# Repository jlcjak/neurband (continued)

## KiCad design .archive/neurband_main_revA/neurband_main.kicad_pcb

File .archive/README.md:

# Archive (`.archive/`)

The folder name starts with a dot so Backplane's project and part lists skip it; git and GitHub still show it.

Older work, kept for reference. Nothing here is current or ordered (every fab file here has
`"order": false`).

| Folder | What it is |
|---|---|
| `neurband_main_revA/` | Rev A main board: 16 channels, ESP32-S3, 54 × 34 mm ([docs/DESIGN.md](../docs/DESIGN.md)) |
| `neurband_main_revB/` | Rev B main board: compact 16 channels, unfinished |
| `neurband_electrodes_revB/` | Rev B electrode flex in four sizes |
| `mech_revAB/` | Rev A/B mechanics: housing, pod shells, strap, fit checks ([docs/mech/mechanical.md](../docs/mech/mechanical.md)). The scripts import `mech/cadutil.py` and `mech/fitgeom.py` |
| `neurband_c_layout_scripts/` | The one-off scripts used while laying out the rev C main board. They record how it was done; the board file itself is now the source. They expect to run from `boards/neurband_c/layout/` |
| `local/` | Local-only backups (working copies, layout build backups); not in git |

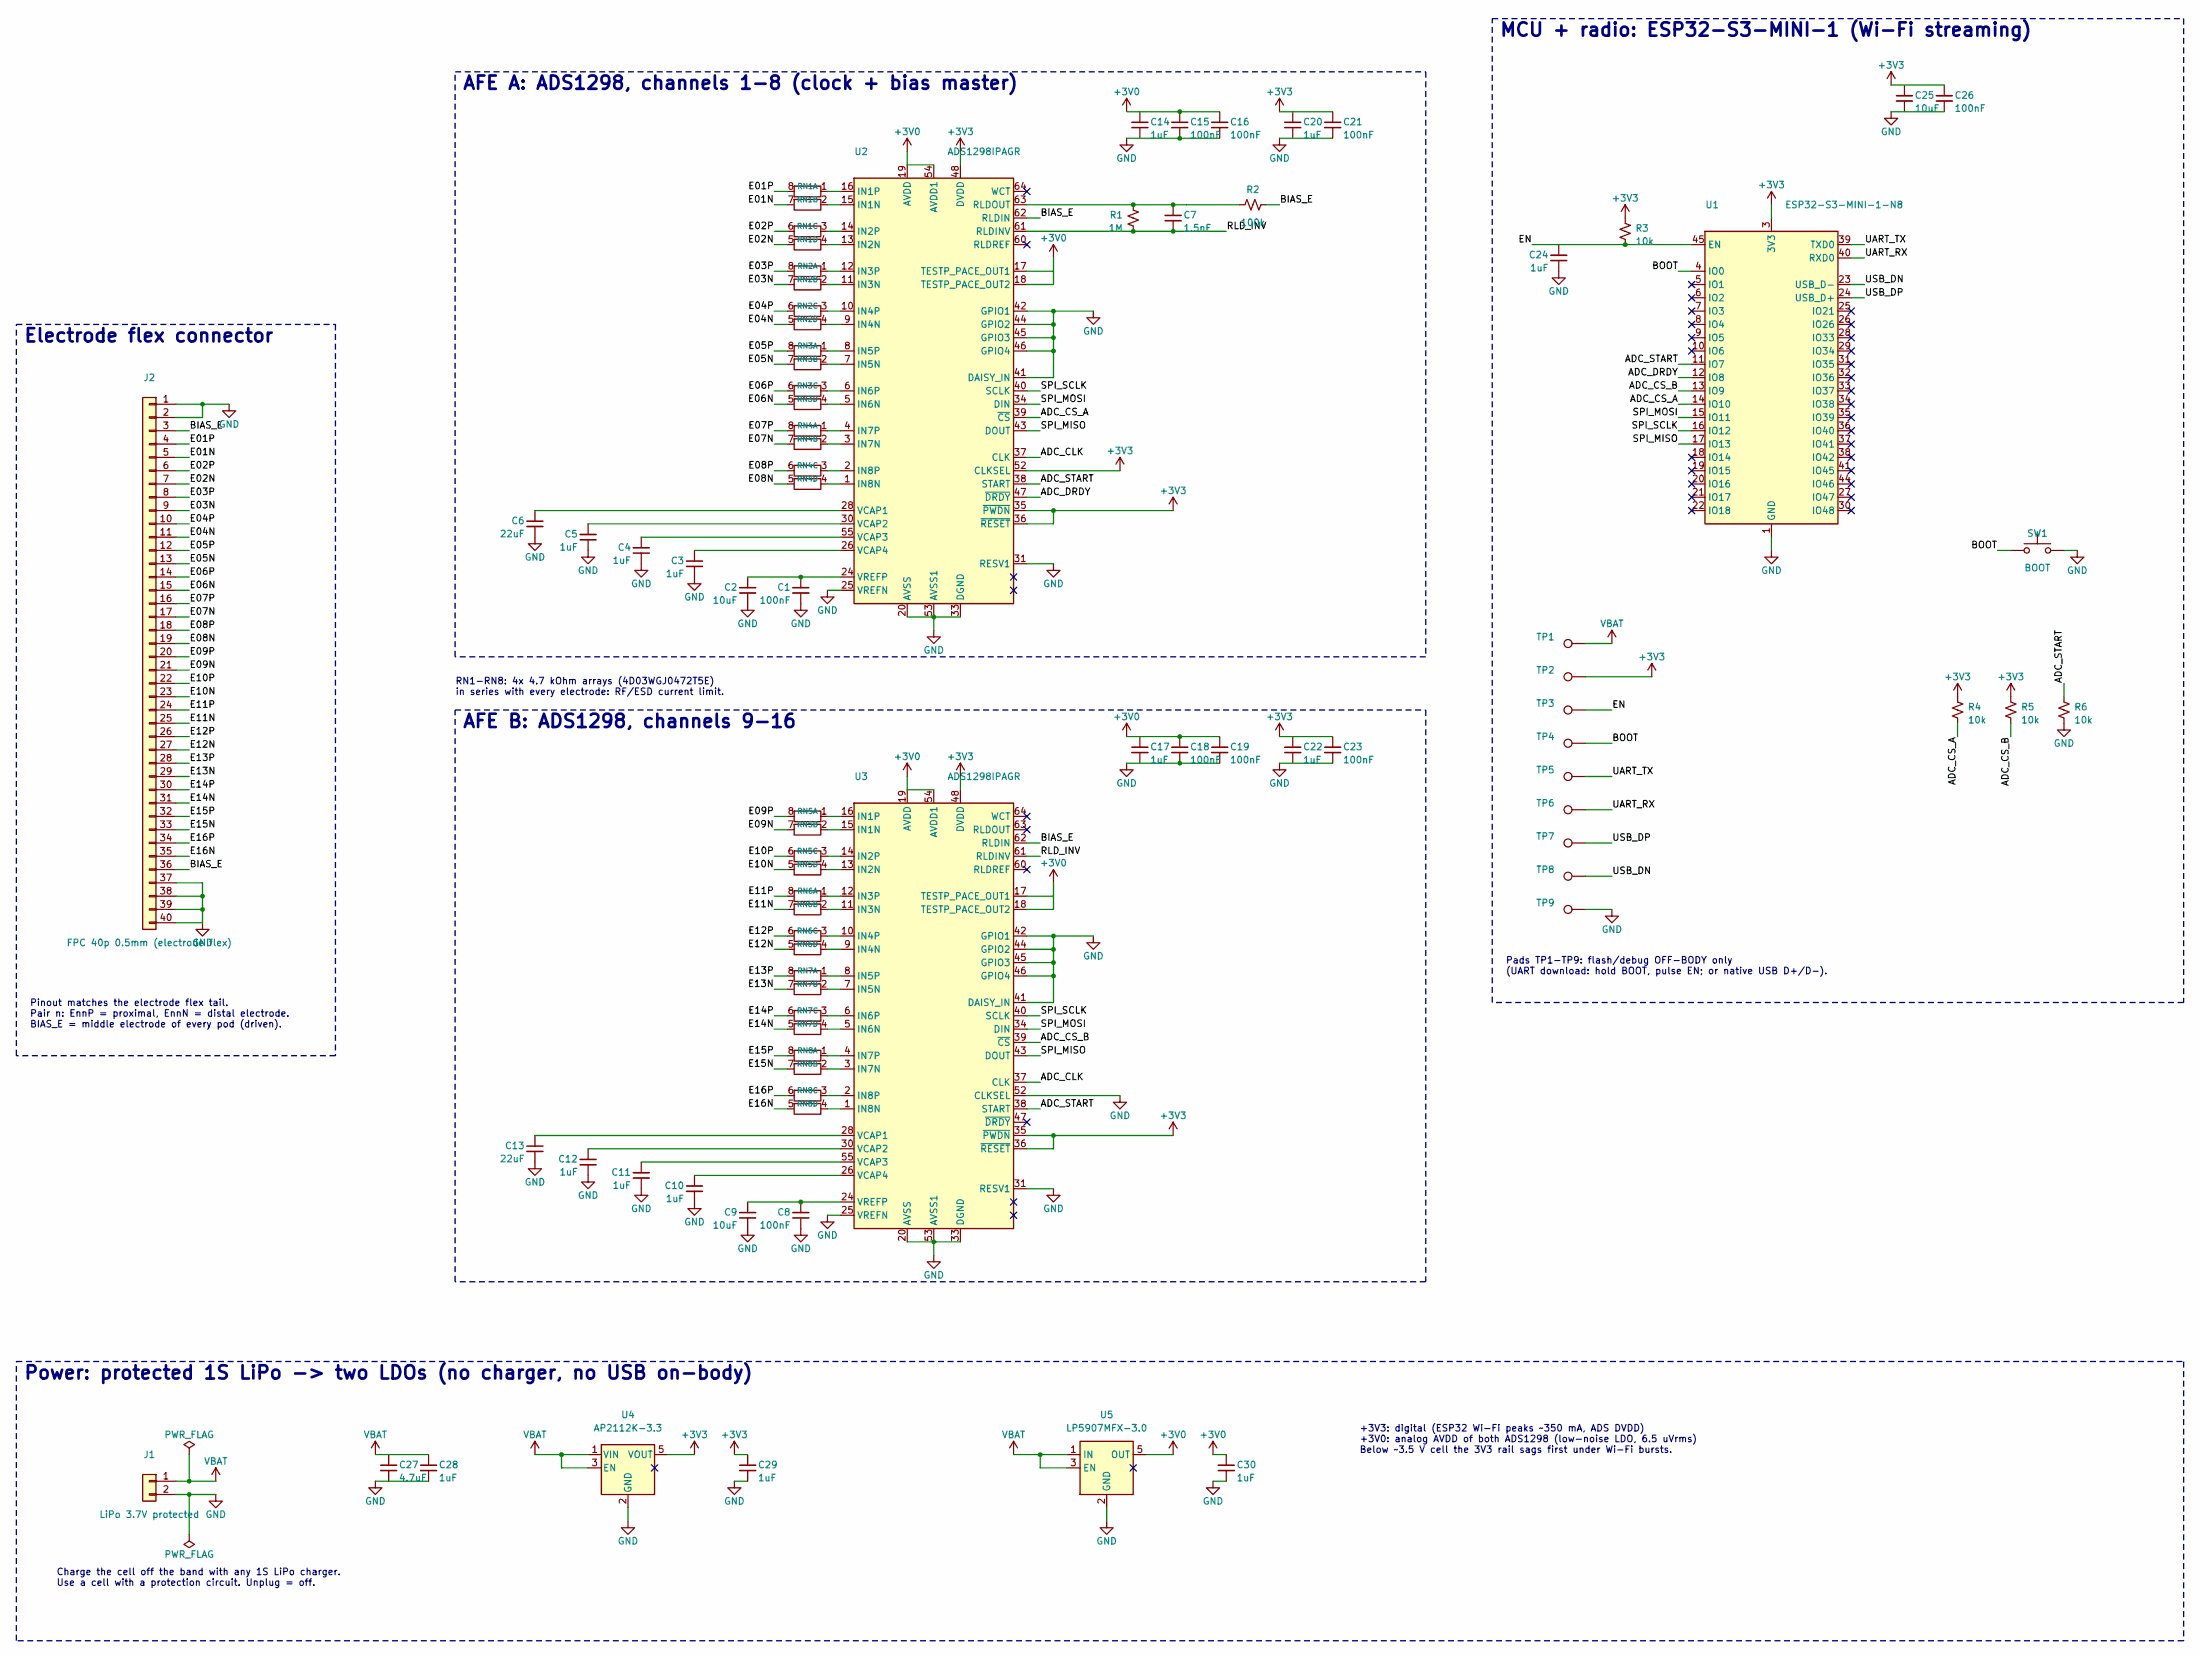
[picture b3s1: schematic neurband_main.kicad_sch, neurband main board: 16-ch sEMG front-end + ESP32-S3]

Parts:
C1, C8, C15, C16, C18, C19, C21, C23, C26: 100nF; C_0402_1005Metric; MPN CL05B104KO5NNNC; LCSC C1525
C2, C9, C25: 10uF; C_0603_1608Metric; MPN CL10A106KP8NNNC; LCSC C19702
C3, C4, C5, C10, C11, C12, C14, C17, C20, C22, C24, C28, C29, C30: 1uF; C_0402_1005Metric; MPN CL05A105KA5NQNC; LCSC C52923
C6, C13: 22uF; C_0603_1608Metric; MPN CL10A226MQ8NRNC; LCSC C59461
C7: 1.5nF; C_0402_1005Metric; MPN CC0402KRX7R9BB152; LCSC C107022
C27: 4.7uF; C_0603_1608Metric; MPN CL10A475KO8NNNC; LCSC C19666
J1: LiPo 3.7V protected; JST_SH_SM02B-SRSS-TB_1x02-1MP_P1.00mm_Horizontal; MPN SM02B-SRSS-TB(LF)(SN); LCSC C160402
J2: FPC 40p 0.5mm (electrode flex); HCTL_HC-FPC-05-09-40RLTAG_1x40-1MP_P0.50mm_Horizontal; MPN HC-FPC-05-09-40RLTAG; LCSC C5213762
R1: 1M; R_0402_1005Metric; MPN 0402WGF1004TCE; LCSC C26083
R2: 100k; R_0402_1005Metric; MPN 0402WGF1003TCE; LCSC C25741
R3, R4, R5, R6: 10k; R_0402_1005Metric; MPN 0402WGF1002TCE; LCSC C25744
RN1, RN2, RN3, RN4, RN5, RN6, RN7, RN8: 4.7k; R_Array_Convex_4x0603; MPN 4D03WGJ0472T5E; LCSC C1980
SW1: BOOT; SW_SPST_TS-1088-xR020; MPN TS-1088-AR02016; LCSC C720477
TP1, TP2, TP3, TP4, TP5, TP6, TP7, TP8, TP9: pad; TestPoint_Pad_1.0x1.0mm
U1: ESP32-S3-MINI-1-N8; MPN ESP32-S3-MINI-1-N8; LCSC C2913206
U2, U3: ADS1298IPAGR; TQFP-64_10x10mm_P0.5mm; MPN ADS1298IPAGR; LCSC C527440
U4: AP2112K-3.3; SOT-23-5; MPN AP2112K-3.3TRG1; LCSC C51118
U5: LP5907MFX-3.0; SOT-23-5; MPN LP5907MFX-3.0/NOPB; LCSC C475492

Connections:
+3V0: C14.1, C15.1, C16.1, C17.1, C18.1, C19.1, C30.1, U2.17 (TESTP_PACE_OUT1), U2.18 (TESTP_PACE_OUT2), U2.19 (AVDD), U2.21 (AVDD), U2.22 (AVDD), U2.54 (AVDD1), U2.56 (AVDD), U2.59 (AVDD), U3.17 (TESTP_PACE_OUT1), U3.18 (TESTP_PACE_OUT2), U3.19 (AVDD), U3.21 (AVDD), U3.22 (AVDD), U3.54 (AVDD1), U3.56 (AVDD), U3.59 (AVDD), U5.5 (OUT)
+3V3: C20.1, C21.1, C22.1, C23.1, C25.1, C26.1, C29.1, R3.1, R4.1, R5.1, TP2.1 (1_1), U1.3 (3V3), U2.35 (~PWDN), U2.36 (~RESET), U2.48 (DVDD), U2.50 (DVDD), U2.52 (CLKSEL), U3.35 (~PWDN), U3.36 (~RESET), U3.48 (DVDD), U3.50 (DVDD), U4.5 (VOUT)
/ADC_CLK: U2.37 (CLK), U3.37 (CLK)
/ADC_CS_A: R4.2, U1.14 (IO10), U2.39 (~CS)
/ADC_CS_B: R5.2, U1.13 (IO9), U3.39 (~CS)
/ADC_DRDY: U1.12 (IO8), U2.47 (~DRDY)
/ADC_START: R6.1, U1.11 (IO7), U2.38 (START), U3.38 (START)
/BIAS_E: J2.3, J2.36, R2.2, U2.62 (RLDIN), U3.62 (RLDIN)
/BOOT: SW1.1, TP4.1 (1_1), U1.4 (IO0)
/E01N: J2.5, RN1.7 (R2.2)
/E01P: J2.4, RN1.8 (R1.2)
/E02N: J2.7, RN1.5 (R4.2)
/E02P: J2.6, RN1.6 (R3.2)
/E03N: J2.9, RN2.7 (R2.2)
/E03P: J2.8, RN2.8 (R1.2)
/E04N: J2.11, RN2.5 (R4.2)
/E04P: J2.10, RN2.6 (R3.2)
/E05N: J2.13, RN3.7 (R2.2)
/E05P: J2.12, RN3.8 (R1.2)
/E06N: J2.15, RN3.5 (R4.2)
/E06P: J2.14, RN3.6 (R3.2)
/E07N: J2.17, RN4.7 (R2.2)
/E07P: J2.16, RN4.8 (R1.2)
/E08N: J2.19, RN4.5 (R4.2)
/E08P: J2.18, RN4.6 (R3.2)
/E09N: J2.21, RN5.7 (R2.2)
/E09P: J2.20, RN5.8 (R1.2)
/E10N: J2.23, RN5.5 (R4.2)
/E10P: J2.22, RN5.6 (R3.2)
/E11N: J2.25, RN6.7 (R2.2)
/E11P: J2.24, RN6.8 (R1.2)
/E12N: J2.27, RN6.5 (R4.2)
/E12P: J2.26, RN6.6 (R3.2)
/E13N: J2.29, RN7.7 (R2.2)
/E13P: J2.28, RN7.8 (R1.2)
/E14N: J2.31, RN7.5 (R4.2)
/E14P: J2.30, RN7.6 (R3.2)
/E15N: J2.33, RN8.7 (R2.2)
/E15P: J2.32, RN8.8 (R1.2)
/E16N: J2.35, RN8.5 (R4.2)
/E16P: J2.34, RN8.6 (R3.2)
/EN: C24.1, R3.2, TP3.1 (1_1), U1.45 (EN)
/RLD_INV: C7.2, R1.2, U2.61 (RLDINV), U3.61 (RLDINV)
/SPI_MISO: U1.17 (IO13), U2.43 (DOUT), U3.43 (DOUT)
/SPI_MOSI: U1.15 (IO11), U2.34 (DIN), U3.34 (DIN)
/SPI_SCLK: U1.16 (IO12), U2.40 (SCLK), U3.40 (SCLK)
/UART_RX: TP6.1 (1_1), U1.40 (RXD0)
/UART_TX: TP5.1 (1_1), U1.39 (TXD0)
/USB_DN: TP8.1 (1_1), U1.23 (USB_D-)
/USB_DP: TP7.1 (1_1), U1.24 (USB_D+)
GND: C1.2, C2.2, C3.2, C4.2, C5.2, C6.2, C8.2, C9.2, C10.2, C11.2, C12.2, C13.2, C14.2, C15.2, C16.2, C17.2, C18.2, C19.2, C20.2, C21.2, C22.2, C23.2, C24.2, C25.2, C26.2, C27.2, C28.2, C29.2, C30.2, J1.2, J2.1, J2.2, J2.37, J2.38, J2.39, J2.40, R6.2, SW1.2, TP9.1 (1_1), U1.1 (GND), U1.2 (GND), U1.42 (GND), U1.43 (GND), U1.46 (GND), U1.47 (GND), U1.48 (GND), U1.49 (GND), U1.50 (GND), U1.51 (GND), U1.52 (GND), U1.53 (GND), U1.54 (GND), U1.55 (GND), U1.56 (GND), U1.57 (GND), U1.58 (GND), U1.59 (GND), U1.60 (GND), U1.61 (GND), U1.62 (GND), U1.63 (GND), U1.64 (GND), U1.65 (GND), U2.20 (AVSS), U2.23 (AVSS), U2.25 (VREFN), U2.31 (RESV1), U2.32 (AVSS), U2.33 (DGND), U2.41 (DAISY_IN), U2.42 (GPIO1), U2.44 (GPIO2), U2.45 (GPIO3), U2.46 (GPIO4), U2.49 (DGND), U2.51 (DGND), U2.53 (AVSS1), U2.57 (AVSS), U2.58 (AVSS), U3.20 (AVSS), U3.23 (AVSS), U3.25 (VREFN), U3.31 (RESV1), U3.32 (AVSS), U3.33 (DGND), U3.41 (DAISY_IN), U3.42 (GPIO1), U3.44 (GPIO2), U3.45 (GPIO3), U3.46 (GPIO4), U3.49 (DGND), U3.51 (DGND), U3.52 (CLKSEL), U3.53 (AVSS1), U3.57 (AVSS), U3.58 (AVSS), U4.2 (GND), U5.2 (GND)
unnamed: RN1.1 (R1.1), U2.16 (IN1P)
unnamed: RN1.2 (R2.1), U2.15 (IN1N)
unnamed: RN1.3 (R3.1), U2.14 (IN2P)
unnamed: RN1.4 (R4.1), U2.13 (IN2N)
unnamed: RN2.1 (R1.1), U2.12 (IN3P)
unnamed: RN2.2 (R2.1), U2.11 (IN3N)
unnamed: RN2.3 (R3.1), U2.10 (IN4P)
unnamed: RN2.4 (R4.1), U2.9 (IN4N)
unnamed: RN3.1 (R1.1), U2.8 (IN5P)
unnamed: RN3.2 (R2.1), U2.7 (IN5N)
unnamed: RN3.3 (R3.1), U2.6 (IN6P)
unnamed: RN3.4 (R4.1), U2.5 (IN6N)
unnamed: RN4.1 (R1.1), U2.4 (IN7P)
unnamed: RN4.2 (R2.1), U2.3 (IN7N)
unnamed: RN4.3 (R3.1), U2.2 (IN8P)
unnamed: RN4.4 (R4.1), U2.1 (IN8N)
unnamed: RN5.1 (R1.1), U3.16 (IN1P)
unnamed: RN5.2 (R2.1), U3.15 (IN1N)
unnamed: RN5.3 (R3.1), U3.14 (IN2P)
unnamed: RN5.4 (R4.1), U3.13 (IN2N)
unnamed: RN6.1 (R1.1), U3.12 (IN3P)
unnamed: RN6.2 (R2.1), U3.11 (IN3N)
unnamed: RN6.3 (R3.1), U3.10 (IN4P)
unnamed: RN6.4 (R4.1), U3.9 (IN4N)
unnamed: RN7.1 (R1.1), U3.8 (IN5P)
unnamed: RN7.2 (R2.1), U3.7 (IN5N)
unnamed: RN7.3 (R3.1), U3.6 (IN6P)
unnamed: RN7.4 (R4.1), U3.5 (IN6N)
unnamed: RN8.1 (R1.1), U3.4 (IN7P)
unnamed: RN8.2 (R2.1), U3.3 (IN7N)
unnamed: RN8.3 (R3.1), U3.2 (IN8P)
unnamed: RN8.4 (R4.1), U3.1 (IN8N)
unnamed: C7.1, R1.1, R2.1, U2.63 (RLDOUT)
unnamed: C6.1, U2.28 (VCAP1)
unnamed: C5.1, U2.30 (VCAP2)
unnamed: C4.1, U2.55 (VCAP3)
unnamed: C3.1, U2.26 (VCAP4)
unnamed: C1.1, C2.1, U2.24 (VREFP)
unnamed: C13.1, U3.28 (VCAP1)
unnamed: C12.1, U3.30 (VCAP2)
unnamed: C11.1, U3.55 (VCAP3)
unnamed: C10.1, U3.26 (VCAP4)
unnamed: C8.1, C9.1, U3.24 (VREFP)
VBAT: C27.1, C28.1, J1.1, TP1.1 (1_1), U4.1 (VIN), U4.3 (EN), U5.1 (IN), U5.3 (EN)

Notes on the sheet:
Electrode flex connector
Pinout matches the electrode flex tail. Pair n: EnnP = proximal, EnnN = distal electrode. BIAS_E = middle electrode of every pod (driven).
RN1-RN8: 4x 4.7 kOhm arrays (4D03WGJ0472T5E) in series with every electrode: RF/ESD current limit.
AFE A: ADS1298, channels 1-8 (clock + bias master)
AFE B: ADS1298, channels 9-16
Pads TP1-TP9: flash/debug OFF-BODY only (UART download: hold BOOT, pulse EN; or native USB D+/D-).
MCU + radio: ESP32-S3-MINI-1 (Wi-Fi streaming)
Charge the cell off the band with any 1S LiPo charger. Use a cell with a protection circuit. Unplug = off.
+3V3: digital (ESP32 Wi-Fi peaks ~350 mA, ADS DVDD) +3V0: analog AVDD of both ADS1298 (low-noise LDO, 6.5 uVrms) Below ~3.5 V cell the 3V3 rail sags first under Wi-Fi bursts.
Power: protected 1S LiPo -> two LDOs (no charger, no USB on-body)

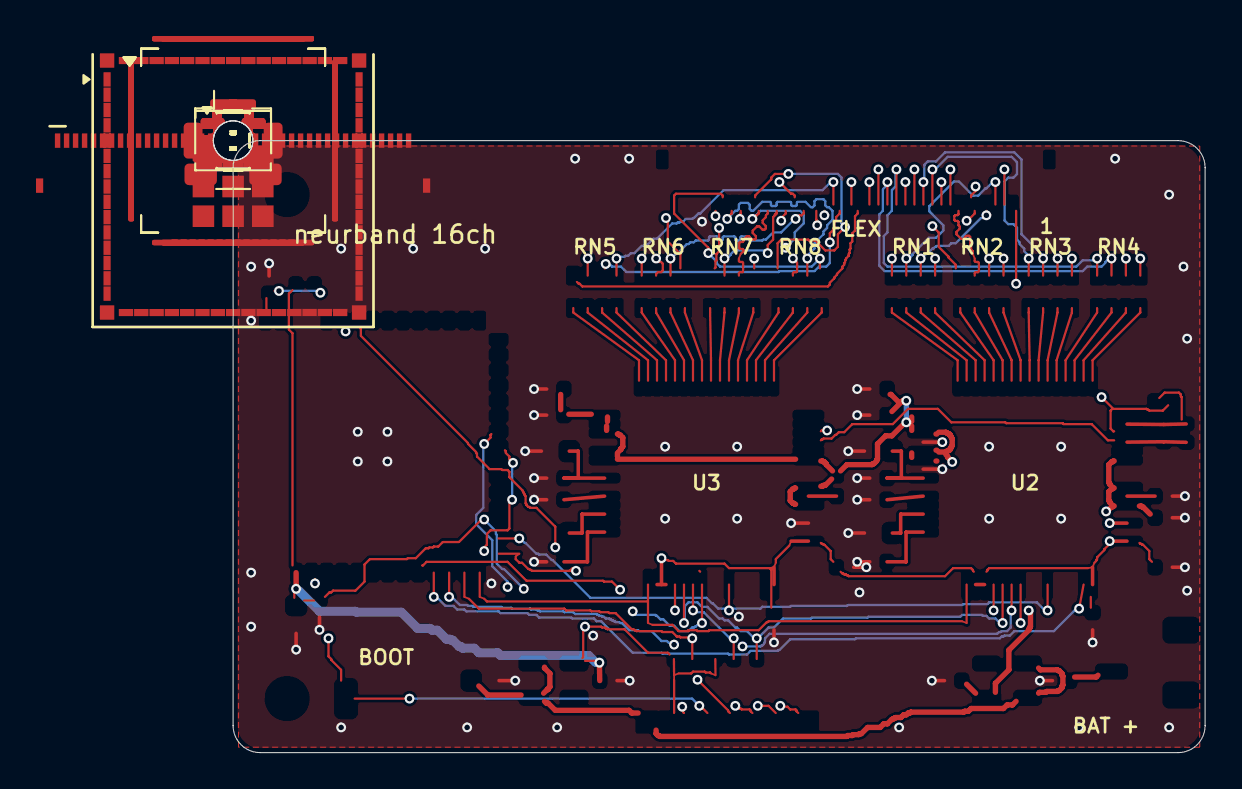
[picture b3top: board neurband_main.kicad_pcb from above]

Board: 4 copper layers, 54.0 x 34.0 mm, 63 parts (0 on the bottom side), 95 nets.

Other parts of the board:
H1, H2: M2; MountingHole_2.2mm_M2

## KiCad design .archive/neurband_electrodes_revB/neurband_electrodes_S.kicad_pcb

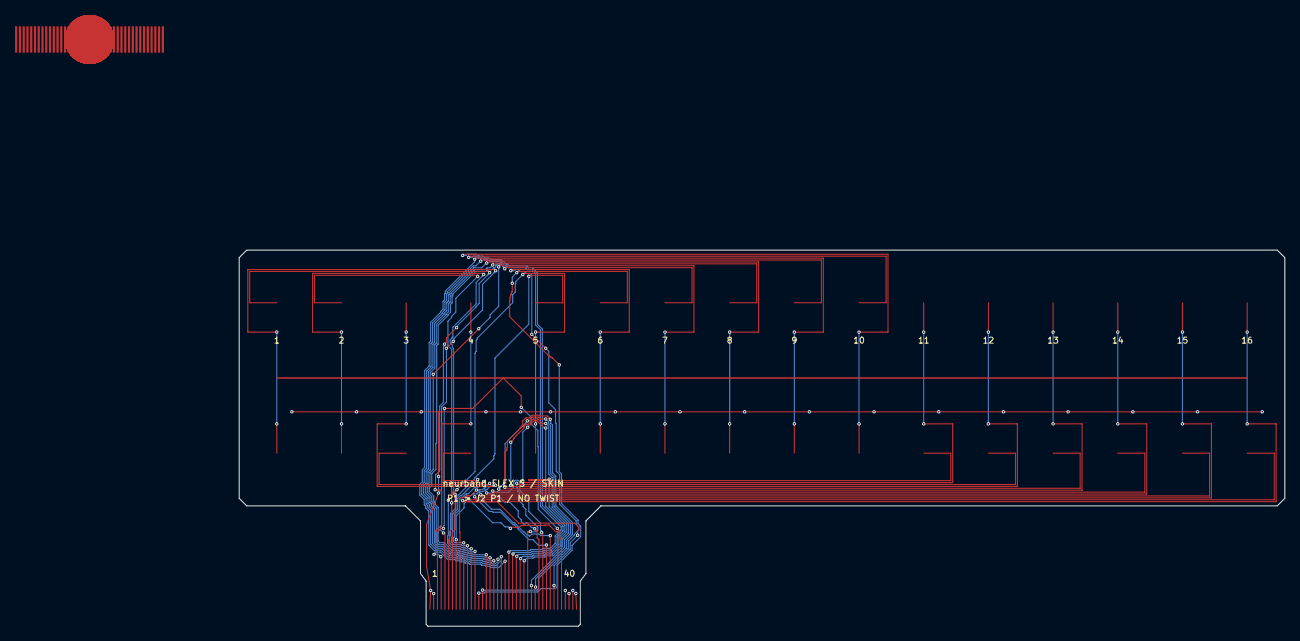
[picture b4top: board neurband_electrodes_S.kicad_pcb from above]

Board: 2 copper layers, 139.0 x 50.0 mm, 49 parts (0 on the bottom side), 34 nets.

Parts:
E1B, E2B, E3B, E4B, E5B, E6B, E7B, E8B, E9B, E10B, E11B, E12B, E13B, E14B, E15B, E16B: electrode B; Electrode_D6.5mm
E1N, E2N, E3N, E4N, E5N, E6N, E7N, E8N, E9N, E10N, E11N, E12N, E13N, E14N, E15N, E16N: electrode N; Electrode_D6.5mm
E1P, E2P, E3P, E4P, E5P, E6P, E7P, E8P, E9P, E10P, E11P, E12P, E13P, E14P, E15P, E16P: electrode P; Electrode_D6.5mm
J1: Tail 40 fingers 0.5mm; FPC_Tail_40_P0.5mm

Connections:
/BIAS_E: E1B.1, E2B.1, E3B.1, E4B.1, E5B.1, E6B.1, E7B.1, E8B.1, E9B.1, E10B.1, E11B.1, E12B.1, E13B.1, E14B.1, E15B.1, E16B.1, J1.3, J1.36
/E01N: E1N.1, J1.5
/E01P: E1P.1, J1.4
/E02N: E2N.1, J1.7
/E02P: E2P.1, J1.6
/E03N: E3N.1, J1.9
/E03P: E3P.1, J1.8
/E04N: E4N.1, J1.11
/E04P: E4P.1, J1.10
/E05N: E5N.1, J1.13
/E05P: E5P.1, J1.12
/E06N: E6N.1, J1.15
/E06P: E6P.1, J1.14
/E07N: E7N.1, J1.17
/E07P: E7P.1, J1.16
/E08N: E8N.1, J1.19
/E08P: E8P.1, J1.18
/E09N: E9N.1, J1.21
/E09P: E9P.1, J1.20
/E10N: E10N.1, J1.23
/E10P: E10P.1, J1.22
/E11N: E11N.1, J1.25
/E11P: E11P.1, J1.24
/E12N: E12N.1, J1.27
/E12P: E12P.1, J1.26
/E13N: E13N.1, J1.29
/E13P: E13P.1, J1.28
/E14N: E14N.1, J1.31
/E14P: E14P.1, J1.30
/E15N: E15N.1, J1.33
/E15P: E15P.1, J1.32
/E16N: E16N.1, J1.35
/E16P: E16P.1, J1.34
GND: J1.1, J1.2, J1.37, J1.38, J1.39, J1.40

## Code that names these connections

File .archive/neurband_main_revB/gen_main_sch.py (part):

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    s.wire([pts[0], pts[-1]])
    for p in pts[1:-1]:
        s.junction(*p)
    if grp[0] == 1:  # pin 3 (BIAS_E) is just below: take GND off the top of the rail
        s.junction(*pts[0])
        s.wire([pts[0], (pts[0][0] + 5.08, pts[0][1])])
        s.power("GND", pts[0][0] + 5.08, pts[0][1])
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    s.power("GND", x, gy1 + 2.54)
    # right side
    s.pin_nc(u, "WCT")
    s.pin_nc(u, "RLDREF")
    s.pin_nc(u, "27")
    s.pin_nc(u, "29")
    # TESTP/TESTN unused -> AVDD (datasheet note 1)
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    s.wire([(t1x + 5.08, t1y), (t2x + 5.08, t2y)])
    s.wire([(t1x + 5.08, t1y), (t1x + 5.08, t1y - 2.54)])
    s.power("+3V0", t1x + 5.08, t1y - 2.54)
    # GPIO1-4 + DAISY_IN unused -> DGND (rail on the right, GND at its top-right)
    rail = []
    for p in ("GPIO1", "GPIO2", "GPIO3", "GPIO4", "DAISY_IN"):
        px, py, _ = u.pin(p)
        s.wire([(px, py), (px + 5.08, py)])
        rail.append((px + 5.08, py))
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    s.wire([(rx, ry), (rx + 5.08, ry)])
    s.power("GND", rx + 5.08, ry)
    # SPI + control
    s.pin_label(u, "SCLK", "SPI_SCLK")
    s.pin_label(u, "DIN", "SPI_MOSI")
    s.pin_label(u, "DOUT", "SPI_MISO")
    s.pin_label(u, "~{CS}", "ADC_CS_A" if master else "ADC_CS_B")
    s.pin_label(u, "START", "ADC_START")
    # PWDN + RESET held high; reset is done with the SPI RESET opcode (master first, then slave once CLK runs)
    p1x, p1y, _ = u.pin("~{PWDN}")
    p2x, p2y, _ = u.pin("~{RESET}")
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    s.junction(p1x + 5.08, p1y)
    s.wire([(p1x + 5.08, p1y), (p1x + 27.94, p1y)])
    s.power("+3V3", p1x + 27.94, p1y)
    s.pin_label(u, "CLK", "ADC_CLK")
    cx_, cy_, _ = u.pin("CLKSEL")
    s.wire([(cx_, cy_), (cx_ + 17.78, cy_)])
    cx_ += 5.08
    if master:
        s.pin_label(u, "~{DRDY}", "ADC_DRDY")
        s.power("+3V3", cx_ + 12.7, cy_)  # internal oscillator, CLK pin drives the slave
    else:
        s.pin_nc(u, "~{DRDY}")
        s.power("GND", cx_ + 12.7, cy_)  # clock taken from master's CLK pin
    # bias (right-leg) drive
    s.pin_label(u, "RLDIN", "BIAS_E")
    ox, oy, _ = u.pin("RLDOUT")
    ix, iy, _ = u.pin("RLDINV")
    if master:
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        s.junction(ox + 20.32, iy)
        s.junction(ox + 27.94, oy)
        s.junction(ox + 27.94, iy)
        s.label("RLD_INV", ix + 38.1, iy, 0)
        rs = passive("R", "100k", ox + 43.18, oy, 90)
        s.wire([(ox + 30.48, oy), (ox + 40.64, oy)])
        s.wire([(ox + 45.72, oy), (ox + 48.26, oy)])
        s.label("BIAS_E", ox + 48.26, oy, 0)
    else:
        s.pin_nc(u, "RLDOUT")  # amplifier powered down; only its RLDINV summing node is shared
        s.pin_label(u, "RLDINV", "RLD_INV")
    return u


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
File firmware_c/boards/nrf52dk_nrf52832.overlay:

/*
 * neurband rev C on the nrf52dk/nrf52832 board definition. Same SoC (nRF52832-QFAA, 32 MHz
 * crystal); everything the DK wires differently is remapped or disabled here.
 * Pin source of truth: boards/neurband_c/gen_c_sch.py (GPIO = {...}).
 *
 * HFXO: the nRF52832 has no internal load capacitors. Y1 (8 pF CL) uses the external 12 pF
 * pair on the board, so nothing is set here. The BLE controller starts the HFXO for every
 * radio event. There is no 32.768 kHz crystal: prj.conf selects the calibrated LFRC.
 */
#include <zephyr/dt-bindings/adc/adc.h>
#include <zephyr/dt-bindings/adc/nrf-saadc.h>

/ {
	chosen {
		/delete-property/ zephyr,console;
		/delete-property/ zephyr,shell-uart;
		/delete-property/ zephyr,uart-mcumgr;
		/delete-property/ zephyr,bt-mon-uart;
		/delete-property/ zephyr,bt-c2h-uart;
	};

	/* The DK LEDs/buttons/PWM LED sit on our START, PWDN, LED, BUTTON and CHG_N pins. */
	aliases {
		/delete-property/ led0;
		/delete-property/ led1;
		/delete-property/ led2;
		/delete-property/ led3;
		/delete-property/ pwm-led0;
		/delete-property/ sw0;
		/delete-property/ sw1;
		/delete-property/ sw2;
		/delete-property/ sw3;
		/delete-property/ mcuboot-button0;
		/delete-property/ mcuboot-led0;
	};
	/delete-node/ leds;
	/delete-node/ pwmleds;
	/delete-node/ buttons;

	zephyr,user {
		led-gpios = <&gpio0 15 GPIO_ACTIVE_LOW>;		/* D1 from +3V3 via 1k into the pin */
		button-gpios = <&gpio0 16 (GPIO_PULL_UP | GPIO_ACTIVE_LOW)>;	/* SW1 to GND */
		chg-gpios = <&gpio0 17 (GPIO_PULL_UP | GPIO_ACTIVE_LOW)>;	/* TP4054 CHRG, open drain */
		io-channels = <&adc 0>;					/* VBAT/2 on AIN4 (P0.28, U1 pin 40) */
	};
};

#ifdef NRF5X_REG_MODE_LDO
/* Zephyr >= 4.0: no DCC inductor on rev C, keep the main regulator in LDO mode. */
&reg {
	regulator-initial-mode = <NRF5X_REG_MODE_LDO>;
};
#endif

&uart0 {
	status = "disabled";
};

/* IMU: ST LSM6DSL on TWI0 (SA0 low -> 0x6A, CS high = I2C mode). IMU pins live only here:
 * I2C_SDA P0.03, I2C_SCL P0.04 (kept off the near-radio pins P0.22-P0.24 bank), IMU_INT (INT1) P0.31. The app drives its registers directly;
 * CONFIG_LSM6DSL=n (prj.conf) keeps Zephyr's own lsm6dsl driver out. CONFIG_SENSOR itself is on:
 * the LFRC calibration selects it for the die temperature sensor (TEMP_NRF5). */
&i2c0 {
	compatible = "nordic,nrf-twi";
	status = "okay";
	clock-frequency = <I2C_BITRATE_FAST>;
	pinctrl-0 = <&i2c0_nb_default>;
	pinctrl-1 = <&i2c0_nb_sleep>;
	pinctrl-names = "default", "sleep";

	lsm6dsl: lsm6dsl@6a {
		compatible = "st,lsm6dsl";
		reg = <0x6a>;
		irq-gpios = <&gpio0 31 GPIO_ACTIVE_HIGH>;
	};
};

&spi1 {
	status = "disabled";
};

&pwm0 {
	status = "disabled";
};

&pinctrl {
	i2c0_nb_default: i2c0_nb_default {
		group1 {
			psels = <NRF_PSEL(TWIM_SDA, 0, 3)>,
				<NRF_PSEL(TWIM_SCL, 0, 4)>;
		};
	};

	i2c0_nb_sleep: i2c0_nb_sleep {
		group1 {
			psels = <NRF_PSEL(TWIM_SDA, 0, 3)>,
				<NRF_PSEL(TWIM_SCL, 0, 4)>;
			low-power-enable;
		};
	};

	spi2_nb_default: spi2_nb_default {
		group1 {
			psels = <NRF_PSEL(SPIM_SCK, 0, 7)>,
				<NRF_PSEL(SPIM_MOSI, 0, 8)>,
				<NRF_PSEL(SPIM_MISO, 0, 11)>;
		};
	};

	spi2_nb_sleep: spi2_nb_sleep {
		group1 {
			psels = <NRF_PSEL(SPIM_SCK, 0, 7)>,
				<NRF_PSEL(SPIM_MOSI, 0, 8)>,
				<NRF_PSEL(SPIM_MISO, 0, 11)>;
			low-power-enable;
		};
	};
};

/* SPIM2 (EasyDMA), mode 1. Register access runs at 1 MHz, frame reads at 8 MHz (ads1298.c). */
&spi2 {
	compatible = "nordic,nrf-spim";
	status = "okay";
	pinctrl-0 = <&spi2_nb_default>;
	pinctrl-1 = <&spi2_nb_sleep>;
	pinctrl-names = "default", "sleep";
	cs-gpios = <&gpio0 6 GPIO_ACTIVE_LOW>;

	ads1298: adc@0 {
		compatible = "ti,ads1298";
		reg = <0>;
		spi-max-frequency = <8000000>;
		drdy-gpios = <&gpio0 12 GPIO_ACTIVE_LOW>;
		start-gpios = <&gpio0 13 GPIO_ACTIVE_HIGH>;
		pwdn-gpios = <&gpio0 14 GPIO_ACTIVE_LOW>;
	};
};

/* Battery: VBAT/2 (1M/1M + 100 nF) on P0.28/AIN4. Gain 1/6 with the 0.6 V reference = 3.6 V
 * full scale; the 100 nF holds the node during the 40 us acquisition. */
&adc {
	#address-cells = <1>;
	#size-cells = <0>;
	status = "okay";

	channel@0 {
		reg = <0>;
		zephyr,gain = "ADC_GAIN_1_6";
		zephyr,reference = "ADC_REF_INTERNAL";
		zephyr,acquisition-time = <ADC_ACQ_TIME(ADC_ACQ_TIME_MICROSECONDS, 40)>;
		zephyr,input-positive = <NRF_SAADC_AIN4>;
		zephyr,resolution = <12>;
		zephyr,oversampling = <4>;
	};
};
